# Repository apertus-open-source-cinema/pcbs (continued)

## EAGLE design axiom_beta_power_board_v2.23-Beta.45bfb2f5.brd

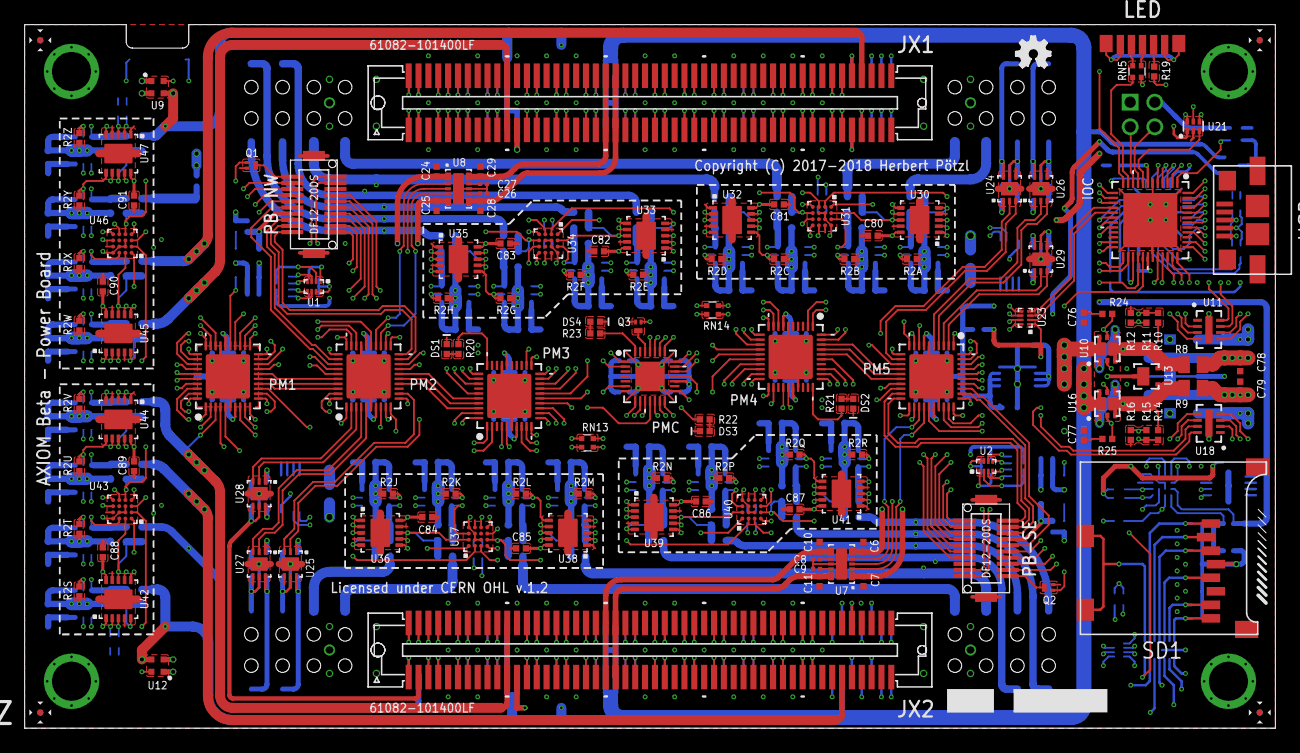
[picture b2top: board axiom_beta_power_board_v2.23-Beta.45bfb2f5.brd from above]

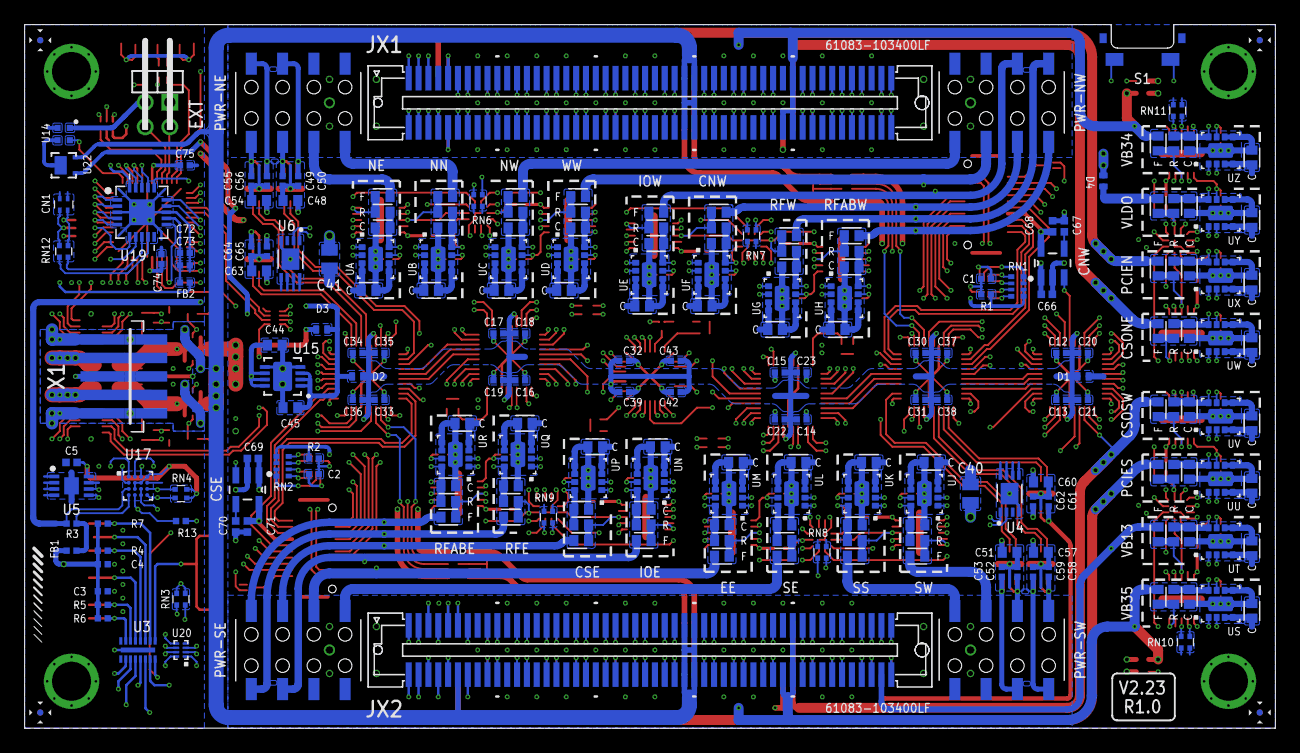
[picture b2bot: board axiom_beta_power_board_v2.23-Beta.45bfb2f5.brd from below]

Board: 4 copper layers, 101.6 x 57.1 mm, 363 parts (231 on the bottom side), 493 nets.

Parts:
BETA: µZ-FCI-SOCKET-NOHOLES-R; µZ-SOCKET-NOHOLES-R
C1, C2, C76, C77, C78, C79: 10n; 0402-C
C1A, C1B, C1C, C1D, C1E, C1F, C1G, C1H, C1J, C1K, C1L, C1M, C1N, C1P, C1Q, C1R, C1S, C1T, C1U, C1V, C1W, C1X, C1Y, C1Z, C2A, C2B, C2C, C2D, C2E, C2F, C2G, C2H, C2J, C2K, C2L, C2M, C2N, C2P, C2Q, C2R, C2S, C2T, C2U, C2V, C2W, C2X, C2Y, C2Z: 0603-C
C3, C49, C50, C52, C53, C55, C56, C58, C59, C61, C62, C64, C65: 1u; 0402-C
C4, C12, C13, C14, C15, C16, C17, C30, C31, C32, C33, C34, C73, C75: 100n; 0402-C
C5: 100n; 0402-B
C6, C7, C10, C11, C24, C25, C28, C29, C80, C81, C82, C83, C84, C85, C86, C87, C88, C89, C90, C91: 0402-C
C8, C9, C26, C27: 0201-C
C18, C19, C20, C21, C22, C23, C35, C36, C37, C38, C39, C72, C74: 4u7; 0402-C
C40, C41: 47u; 0805-C
C42, C43: 10u; 0402-C
C44, C45: 10u; 0603-C
C48, C51, C54, C57, C60, C63: 4u7; 0603-C
C66, C68, C69, C71: 1u; 0402-B
C67, C70: 10n; 0402-B
CN1: CC0504
CNW: SPX3819M5-L; SOT95P280X145-5N
CSE: SPX3819M5-L; SOT95P280X145-5N
D1, D2, D3, D4: PMEG2010BELD; DFN1006D-2
DS1, DS2, DS3, DS4: 0402-C
EXT: 2X02M/90-S
F1, F2, F3, F4, F5, F6, F7, F8: FIDUCIAL; FID_ARROW
FB1, FB2: 0402-C
FBA: 0603-C
FBB: 0603-C
FBC: 0603-C
FBD: 0603-C
FBE: 0603-C
FBF: 0603-C
FBG: 0603-C
FBH: 0603-C
FBJ: 0603-C
FBK: 0603-C
FBL: 0603-C
FBM: 0603-C
FBN: 0603-C
FBP: 0603-C
FBQ: 0603-C
FBR: 0603-C
FBS: 0603-C
FBT: 0603-C
FBU: 0603-C
FBV: 0603-C
FBW: 0603-C
FBX: 0603-C
FBY: 0603-C
FBZ: 0603-C
IOC: PIC16F15386; UQFN50P600X600X100-49N-NSM
LED: MSL0104RGB; MSL0104-SL
LOGO1: OSHW_LOGO_FILLX0100-NT; OSHW_FILLX100_NOTEXT
PB-NW: DF12(XX)-20DP-0.5V
PB-SE: DF12(XX)-20DP-0.5V
PM1, PM2, PM3, PM4, PM5: PIC16F1779-NSM; UQFN40P500X500X100-41N-NSM
PMC: PIC16F15356; UQFN50P400X400X100-29N-NSM
PWR-NE: PINRC-2X04; R2X04
PWR-NW: PINRC-2X04; R2X04
PWR-SE: PINRC-2X04; R2X04
PWR-SW: PINRC-2X04; R2X04
Q1, Q2, Q3: NX3008NBKMB; SOT883(B)
R1, R2: 200k; 0402-C
R1A, R1B, R1C, R1D, R1E, R1F, R1G, R1H, R1J, R1K, R1L, R1M, R1N, R1P, R1Q, R1R, R1S, R1T, R1U, R1V, R1W, R1X, R1Y, R1Z: 0603-C
R2A, R2B, R2C, R2D, R2E, R2F, R2G, R2H, R2J, R2K, R2L, R2M, R2N, R2P, R2Q, R2R, R2S, R2T, R2U, R2V, R2W, R2X, R2Y, R2Z, R3, R13, R19, R20, R21, R22, R23: 0402-C
R4, R5, R6, R7: 50k; 0402-C
R8, R9: 0805-C
R10, R14: 243k; 0402-C
R11, R15, R24, R25: 5k11; 0402-C
R12, R16: 24k9; 0402-C
RN1, RN2: 4X0402ARV341
RN3, RN4, RN5, RN6, RN7, RN8, RN9, RN10, RN11, RN12, RN13, RN14: EXB24V
S1: SKSNLAE010
SD1: MICRO-SD-2CD; TF-MICRO-SD_PP2
U1, U2: PCA9306; UDFN-8
U3: IP4251CZ16-8-TTL; SON40P135X330X55-17N
U4, U6: MCP9808; DFN-8
U5: BR24G04NUX; DFN200X300X100-9N
U7, U8: AP22966; V-DFN3020-14
U9, U12, U14: MIC94040; MLF-4
U10, U16: NTLUD4C26N; UDFN6
U11, U18: LTC4365; DFN8
U13, U22: PMEG2020CPAS; DFN2020D-3
U15: LT1965; DFN3X3_8LEAD
U17, U31, U34, U37, U40, U43, U46: PAC1934-LP; WLCSP-16-LP
U19: FT231-NSM; QFN65P400X400X100-21N-NSM
U20, U23: TXS0102; X2SON-8
U21: FXLH1T45; MICROPAK-6
U24, U25, U26, U27, U28, U29: AP7312-3333FM-7; DFN2018-6
U30, U32, U33, U35, U36, U38, U39, U41, U42, U44, U45, U47: MCP46X2; DFN-10
UA: TPS82085; MICROSIP
UB: TPS82085; MICROSIP
UC: TPS82085; MICROSIP
UD: TPS82085; MICROSIP
UE: TPS82085; MICROSIP
UF: TPS82085; MICROSIP
UG: TPS82085; MICROSIP
UH: TPS82085; MICROSIP
UJ: TPS82085; MICROSIP
UK: TPS82085; MICROSIP
UL: TPS82085; MICROSIP
UM: TPS82085; MICROSIP
UN: TPS82085; MICROSIP
UP: TPS82085; MICROSIP
UQ: TPS82085; MICROSIP
UR: TPS82085; MICROSIP
US: TPS82085; MICROSIP
USB: 5_USB_3S; MICRO-AB-H-SMT
UT: TPS82085; MICROSIP
UU: TPS82085; MICROSIP
UV: TPS82085; MICROSIP
UW: TPS82085; MICROSIP
UX: TPS82085; MICROSIP
UY: TPS82085; MICROSIP
UZ: TPS82085; MICROSIP
X1: PICO-SPOX-5
ZED: µZ-FCI-CONONLY; µZ-CONONLY

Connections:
!ALERT: PM5.22, U17.C3, U17.D3
!MCLR_1: PM1.16, PM2.36
!MCLR_2: PM2.16, PM3.36
!MCLR_3: PM3.16, PMC.2
!MCLR_4: PM4.16, PMC.1
!MCLR_5: PM4.36, PM5.16
!MCLR_C: PMC.26, Q3.3
!RESET: IOC.27, U19.11
ANY_IN: C44.1, U13.3, U13.4, U15.6, U15.7, U15.8
A_!RST: PB-NW.1, Q1.3
A_RST: PM2.25, Q1.1
A_SCL: PB-NW.2, RN1.1, U1.3
A_SDA: PB-NW.4, RN1.2, U1.4
BACK_1: PM1.13, PMC.10
BACK_5: PM5.13, PMC.18
BANK13_00_N: BETA.89, ZED.89
BANK13_00_P: BETA.87, ZED.87
BANK13_01_N: BETA.90, ZED.90
BANK13_01_P: BETA.88, ZED.88
BANK13_02_N: BETA.93, ZED.93
BANK13_02_P: BETA.91, ZED.91
BANK13_03_N: BETA.94, ZED.94
BANK13_03_P: BETA.92, ZED.92
BANK13_04_N: BETA.195, ZED.195
BANK13_04_P: BETA.193, ZED.193
BANK13_05_N: BETA.196, ZED.196
BANK13_05_P: BETA.194, ZED.194
BANK13_06_N: BETA.199, ZED.199
BANK13_06_P: BETA.197, ZED.197
BANK13_SE_0: BETA.200, ZED.200
BETA_5V: C1A.1, C1B.1, C1C.1, C1D.1, C1E.1, C1F.1, C1G.1, C1H.1, C1J.1, C1K.1, C1L.1, C1M.1, C1N.1, C1P.1, C1Q.1, C1R.1, C1S.1, C1T.1, C1U.1, C1V.1, C1W.1, C1X.1, C1Y.1, C1Z.1, C5.1, C6.1, C7.1, C24.1, C25.1, C40.1, C41.1, C80.1, C81.1, C82.1, C83.1, C84.1, C85.1, C86.1, C87.1, C88.1, C89.1, C90.1, C91.1, D1.A, RN4.3, RN4.4, RN6.3, RN6.4, RN7.3, RN7.4, RN8.3, RN8.4, RN9.3, RN9.4, RN10.3, RN10.4, RN11.3, RN11.4, U4.5, U4.6, U4.7, U4.8, U5.8, U6.5, U6.6, U6.7, U6.8, U7.1, U7.3, U7.5, U8.1, U8.3, U8.5, U10.6, U10.D1, U11.6, U17.A4, U17.B2, U17.B3, U17.C2, U30.1, U30.10, U31.A4, U31.B2, U31.B3, U31.C2, U32.9, U32.10, U33.1, U33.10, U34.A4, U34.B2, U34.B3, U34.C2, U35.9, U35.10, U36.1, U36.10, U37.A4, U37.B2, U37.B3, U37.C2, U38.9, U38.10, U39.1, U39.10, U40.A4, U40.B2, U40.B3, U40.C2, U41.9, U41.10, U42.1, U42.10, U43.A4, U43.B2, U43.B3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
BETA_!FAULT: IOC.40, U11.7
BETA_!SHDN: IOC.37, U11.8
BETA_GATE: R24.1, U10.2, U10.5, U11.5
BETA_IN: R8.2, R10.1, U10.3, U10.D2, U11.4, U13.2, U17.B1
BETA_OV: R11.2, R12.1, U11.2
BETA_SUP: C78.1, R8.1, U17.A1, X1.4, X1.4A
BETA_UV: R10.2, R11.1, U11.3
BTN: PM1.20, S1.2
B_!RST: PB-SE.1, Q2.3
B_RST: PM5.25, Q2.1
B_SCL: PB-SE.2, RN2.1, U2.3
B_SDA: PB-SE.4, RN2.2, U2.4
CBUS3: IOC.28, U19.16
CC_!MCLR: IOC.20, U19.7
CC_JX1: IOC.8, U21.3
CC_PCLK: IOC.18, U19.15
CC_PDAT: IOC.19, U19.14
CC_SE_0: IOC.47, U20.6
CC_SE_1: IOC.48, U20.7
CD: SD1.CD1, SD1.CD2, U3.1
CD': IOC.26, U3.16
CLK: SD1.5, U3.5
CMD: R4.2, SD1.3, U3.4
CNW_BYP: C67.1, CNW.4
CNW_EN: CNW.3, PM1.25
CSE_BYP: C70.1, CSE.4
CSE_EN: CSE.3, PM5.36
CSO_NE_V: BETA.7, FBX.2, PM1.37
CSO_NW_V: FBF.2, PM3.32, PWR-NW.6
CSO_SE_V: FBP.2, PM4.32, PWR-SE.6
CSO_SW_V: BETA.112, FBU.2, PM1.2
D0: IOC.5, U19.17
D1: IOC.45, U19.1
D2: IOC.3, U19.19
D3: IOC.2, U19.6
D4: IOC.4, U19.18
D5: IOC.43, U19.4
D6: IOC.42, U19.5
D7: IOC.44, U19.2
DAT0: R5.2, SD1.7, U3.6
DAT1: R6.2, SD1.8, U3.7
DAT2: R7.2, SD1.1, U3.2
DAT3: SD1.2, U3.3
DM: RN12.3, U19.9
DP: RN12.4, U19.8
DS1: PM3.30, R20.1
DS2: PM4.30, R21.1
DS3: PMC.6, R22.1
DS4: PMC.28, R23.1
DXP_0_N: BETA.100, ZED.100
DXP_0_P: BETA.98, ZED.98
EN_3: PM2.24, U8.2
EN_4: PM2.23, U8.4
EN_5: PM5.24, U7.2
EN_6: PM5.23, U7.4
EN_A: PM4.40, UA.1
EN_B: PM4.2, UB.1
EN_C: PM4.10, UC.1
EN_D: PM4.12, UD.1
EN_E: PM3.18, UE.1
EN_F: PM3.20, UF.1
EN_G: PM3.22, UG.1
EN_H: PM3.33, UH.1
EN_J: PM3.40, UJ.1
EN_K: PM3.2, UK.1
EN_L: PM3.10, UL.1
EN_M: PM3.12, UM.1
EN_N: PM4.18, UN.1
EN_P: PM4.20, UP.1
EN_Q: PM4.22, UQ.1
EN_R: PM4.33, UR.1
EN_S: PM1.17, US.1
EN_T: PM1.5, UT.1
EN_U: PM1.4, UU.1
EN_V: PM1.36, UV.1
EN_W: PM1.34, UW.1
EN_X: PM1.30, UX.1
EN_Y: PM1.28, UY.1
EN_Z: PM1.21, UZ.1
EXTA: EXT.2, IOC.10
EXTB: EXT.4, IOC.9
E_B_SCL: PM5.31, RN2.4, U2.6
E_B_SDA: PM5.30, RN2.3, U2.5
E_I2C_EN: PM5.17, U24.2
E_I2C_V: C50.1, PWR-NE.6, U24.6
E_SPI_EN: PM5.5, U26.2
E_SPI_V: C56.1, PWR-NE.8, U26.6
E_VE: FBM.2, PM5.21, PWR-SE.4
E_VE_CV: PB-SE.20, PM5.18
E_VE_OV: PB-SE.9, PM5.10
E_VE_UV: PB-SE.11, PM5.33
FAN_SUP: EXT.3, U14.1
FAN_SUP_EN: IOC.1, U14.4
FB_A: R2A.2, U30.6, UA.7
FB_B: R2B.2, U30.7, UB.7
FB_C: R2C.2, U32.6, UC.7
FB_D: R2D.2, U32.7, UD.7
FB_E: R2E.2, U33.6, UE.7
FB_F: R2F.2, U33.7, UF.7
FB_G: R2G.2, U35.6, UG.7
FB_H: R2H.2, U35.7, UH.7
FB_J: R2J.2, U36.6, UJ.7
FB_K: R2K.2, U36.7, UK.7
FB_L: R2L.2, U38.6, UL.7
FB_M: R2M.2, U38.7, UM.7
FB_N: R2N.2, U39.6, UN.7
FB_P: R2P.2, U39.7, UP.7
FB_Q: R2Q.2, U41.6, UQ.7
FB_R: R2R.2, U41.7, UR.7
FB_S: R2S.2, U42.6, US.7
FB_T: R2T.2, U42.7, UT.7
FB_U: R2U.2, U44.6, UU.7
FB_V: R2V.2, U44.7, UV.7
FB_W: R2W.2, U45.6, UW.7
FB_X: R2X.2, U45.7, UX.7
FB_Y: R2Y.2, U47.6, UY.7
FB_Z: R2Z.2, U47.7, UZ.7
GND: BETA.15, BETA.16, BETA.21, BETA.22, BETA.27, BETA.28, BETA.33, BETA.34, BETA.39, BETA.40, BETA.45, BETA.46, BETA.51, BETA.52, BETA.65, BETA.66, BETA.71, BETA.72, BETA.77, BETA.85, BETA.86, BETA.95, BETA.96, BETA.115, BETA.116, BETA.121, BETA.122, BETA.127, BETA.128, BETA.133, BETA.134, BETA.139, BETA.140, BETA.145, BETA.146, BETA.151, BETA.152, BETA.165, BETA.166, BETA.171, BETA.172, BETA.177, BETA.185, BETA.186, BETA.191, BETA.192, C1.2, C1A.2, C1B.2, C1C.2, C1D.2, C1E.2, C1F.2, C1G.2, C1H.2, C1J.2, C1K.2, C1L.2, C1M.2, C1N.2, C1P.2, C1Q.2, C1R.2, C1S.2, C1T.2, C1U.2, C1V.2, C1W.2, C1X.2, C1Y.2, C1Z.2, C2.2, C2A.2, C2B.2, C2C.2, C2D.2, C2E.2, C2F.2, C2G.2, C2H.2, C2J.2, C2K.2, C2L.2, C2M.2, C2N.2, C2P.2, C2Q.2, C2R.2, C2S.2, C2T.2, C2U.2, C2V.2, C2W.2, C2X.2, C2Y.2, C2Z.2, C3.2, C4.2, C5.2, C6.2, C7.2, C8.2, C9.2, C10.2, C11.2, C12.2, C13.2, C14.2, C15.2, C16.2, C17.2, C18.2, C19.2, C20.2, C21.2, C22.2, C23.2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
IOE_V: FBN.2, PM4.35, PWR-SE.5, RN2.7, RN2.8, U2.2
IOW_V: FBE.2, PM3.35, PWR-NW.5, RN1.7, RN1.8, U1.2
JTAG_EN: PM2.5, U27.2
JTAG_V: C59.1, PWR-SW.8, U27.6
JX1_00_N: BETA.13, ZED.13
JX1_00_P: BETA.11, ZED.11
JX1_01_N: BETA.14, ZED.14
JX1_01_P: BETA.12, ZED.12
JX1_02_N: BETA.19, ZED.19
JX1_02_P: BETA.17, ZED.17
JX1_03_N: BETA.20, ZED.20
JX1_03_P: BETA.18, ZED.18
JX1_04_N: BETA.25, ZED.25
JX1_04_P: BETA.23, ZED.23
JX1_05_N: BETA.26, ZED.26
JX1_05_P: BETA.24, ZED.24
JX1_06_N: BETA.31, ZED.31
JX1_06_P: BETA.29, ZED.29
JX1_07_N: BETA.32, ZED.32
JX1_07_P: BETA.30, ZED.30
JX1_08_N: BETA.37, ZED.37
JX1_08_P: BETA.35, ZED.35
JX1_09_N: BETA.38, ZED.38
JX1_09_P: BETA.36, ZED.36
JX1_10_N: BETA.43, ZED.43
JX1_10_P: BETA.41, ZED.41
JX1_11_N: BETA.44, ZED.44
JX1_11_P: BETA.42, ZED.42
JX1_12_N: BETA.49, ZED.49
JX1_12_P: BETA.47, ZED.47
JX1_13_N: BETA.50, ZED.50
JX1_13_P: BETA.48, ZED.48
JX1_14_N: BETA.55, ZED.55
JX1_14_P: BETA.53, ZED.53
JX1_15_N: BETA.56, ZED.56
JX1_15_P: BETA.54, ZED.54
JX1_16_N: BETA.63, ZED.63
JX1_16_P: BETA.61, ZED.61
JX1_17_N: BETA.64, ZED.64
JX1_17_P: BETA.62, ZED.62
JX1_18_N: BETA.69, ZED.69
JX1_18_P: BETA.67, ZED.67
JX1_19_N: BETA.70, ZED.70
JX1_19_P: BETA.68, ZED.68
JX1_20_N: BETA.75, ZED.75
JX1_20_P: BETA.73, ZED.73
JX1_21_N: BETA.76, ZED.76
JX1_21_P: BETA.74, ZED.74
JX1_22_N: BETA.83, ZED.83
JX1_22_P: BETA.81, ZED.81
JX1_23_N: BETA.84, ZED.84
JX1_23_P: BETA.82, ZED.82
JX1_DIR: IOC.38, U21.5
JX1_SE_0: BETA.9, ZED.9
JX1_SE_1: BETA.10, U21.4, ZED.10
JX2_00_N: BETA.119, ZED.119
JX2_00_P: BETA.117, ZED.117
JX2_01_N: BETA.120, ZED.120
JX2_01_P: BETA.118, ZED.118
JX2_02_N: BETA.125, ZED.125
JX2_02_P: BETA.123, ZED.123
JX2_03_N: BETA.126, ZED.126
JX2_03_P: BETA.124, ZED.124
JX2_04_N: BETA.131, ZED.131
JX2_04_P: BETA.129, ZED.129
JX2_05_N: BETA.132, ZED.132
JX2_05_P: BETA.130, ZED.130
JX2_06_N: BETA.137, ZED.137
JX2_06_P: BETA.135, ZED.135
JX2_07_N: BETA.138, ZED.138
JX2_07_P: BETA.136, ZED.136
JX2_08_N: BETA.143, ZED.143
JX2_08_P: BETA.141, ZED.141
JX2_09_N: BETA.144, ZED.144
JX2_09_P: BETA.142, ZED.142
JX2_10_N: BETA.149, ZED.149
JX2_10_P: BETA.147, ZED.147
JX2_11_N: BETA.150, ZED.150
JX2_11_P: BETA.148, ZED.148
JX2_12_N: BETA.155, ZED.155
JX2_12_P: BETA.153, ZED.153
JX2_13_N: BETA.156, ZED.156
JX2_13_P: BETA.154, ZED.154
JX2_14_N: BETA.163, ZED.163
JX2_14_P: BETA.161, ZED.161
JX2_15_N: BETA.164, ZED.164
JX2_15_P: BETA.162, ZED.162
JX2_16_N: BETA.169, ZED.169
JX2_16_P: BETA.167, ZED.167
JX2_17_N: BETA.170, ZED.170
JX2_17_P: BETA.168, ZED.168
JX2_18_N: BETA.175, ZED.175
JX2_18_P: BETA.173, ZED.173
JX2_19_N: BETA.176, ZED.176
JX2_19_P: BETA.174, ZED.174
JX2_20_N: BETA.183, ZED.183
JX2_20_P: BETA.181, ZED.181
JX2_21_N: BETA.184, ZED.184
JX2_21_P: BETA.182, ZED.182
JX2_22_N: BETA.189, ZED.189
JX2_22_P: BETA.187, ZED.187
JX2_23_N: BETA.190, ZED.190
JX2_23_P: BETA.188, ZED.188
JX2_SE_0: U20.3, ZED.113
JX2_SE_1: U20.2, ZED.114
LED_B: IOC.11, RN5.3
LED_G: IOC.33, R19.2
LED_G': LED.3, R19.1
LED_R: IOC.32, RN5.4
MEAS_A: FBA.1, R1A.2, U30.5, U31.B1
MEAS_B: FBB.1, R1B.2, U30.8, U31.A2
MEAS_C: FBC.1, R1C.2, U31.D2, U32.5
MEAS_D: FBD.1, R1D.2, U31.C1, U32.8
MEAS_E: FBE.1, R1E.2, U33.5, U34.B1
MEAS_F: FBF.1, R1F.2, U33.8, U34.A2
MEAS_G: FBG.1, R1G.2, U34.D2, U35.5
MEAS_H: FBH.1, R1H.2, U34.C1, U35.8
MEAS_J: FBJ.1, R1J.2, U36.5, U37.B1
MEAS_K: FBK.1, R1K.2, U36.8, U37.A2
MEAS_L: FBL.1, R1L.2, U37.D2, U38.5
MEAS_M: FBM.1, R1M.2, U37.C1, U38.8
MEAS_N: FBN.1, R1N.2, U39.5, U40.B1
MEAS_P: FBP.1, R1P.2, U39.8, U40.A2
MEAS_Q: FBQ.1, R1Q.2, U40.D2, U41.5
MEAS_R: FBR.1, R1R.2, U40.C1, U41.8
MEAS_S: FBS.1, R1S.2, U42.5, U43.B1
MEAS_T: FBT.1, R1T.2, U42.8, U43.A2
MEAS_U: FBU.1, R1U.2, U43.D2, U44.5
MEAS_V: FBV.1, R1V.2, U43.C1, U44.8
MEAS_W: FBW.1, R1W.2, U45.5, U46.B1
MEAS_X: FBX.1, R1X.2, U45.8, U46.A2
MEAS_Y: FBY.1, R1Y.2, U46.D2, U47.5
MEAS_Z: FBZ.1, R1Z.2, U46.C1, U47.8
MIX_SUP: U14.3, U22.3, U22.4
unnamed: DS2.1, R21.2
unnamed: DS4.1, R23.2
unnamed: C3.1, C4.1, FB1.2, R4.1, R5.1, R6.1, R7.1, SD1.4
unnamed: LED.4, RN5.1
unnamed: C76.1, R24.2
unnamed: LED.5, RN5.2
unnamed: CN1.3, RN12.2, USB.2
unnamed: C77.1, R25.2
unnamed: CN1.4, RN12.1, USB.3
unnamed: U10.1, U10.4
unnamed: C26.1, U8.7
unnamed: C27.1, U8.9
unnamed: C8.1, U7.7
unnamed: C9.1, U7.9
unnamed: DS1.1, R20.2
unnamed: DS3.1, R22.2
unnamed: C1.1, R1.2, U1.7, U1.8
unnamed: C2.1, R2.2, U2.7, U2.8
unnamed: U16.1, U16.4
N_CHK_V: C68.1, CNW.5, PB-NW.13
N_I2C_EN: PM5.4, U26.3
N_I2C_V: C55.1, PWR-NE.7, U26.5
N_SPI_EN: PM5.12, U24.3
N_SPI_V: C49.1, PWR-NE.5, U24.5
N_VE: FBA.2, PWR-NE.3
N_VE_CV: PB-NW.18, PM2.9
N_VE_OV: PB-NW.7, PM2.8
N_VE_RS: PB-NW.8, PM2.11
N_VE_UV: PB-NW.19, PM2.19
N_VN: FBB.2, PWR-NE.1
N_VN_CV: PB-NW.16, PM2.35
N_VN_OV: PB-NW.5, PM2.29
N_VN_RS: PB-NW.12, PM2.34
N_VN_UV: PB-NW.17, PM2.20
N_VW: FBC.2, PWR-NW.2
N_VW_CV: PB-NW.14, PM2.40
N_VW_OV: PB-NW.3, PM2.28
N_VW_RS: PB-NW.10, PM2.39
N_VW_UV: PB-NW.15, PM2.32
PCIE_I2C_EN: PM2.2, U28.3
PCIE_I2C_V: BETA.198, C61.1, U28.5
PCIE_NIO_EN: PM1.23, U9.4
PCIE_N_5V: BETA.59, BETA.60, C29.1, U8.10
PCIE_N_V: BETA.79, BETA.80, FBW.2, PM1.11
PCIE_N_VCCIO: BETA.78, U9.1
PCIE_SIO_EN: PM1.24, U12.4
PCIE_S_5V: BETA.159, BETA.160, C10.1, U7.6
PCIE_S_V: BETA.179, BETA.180, FBV.2, PM1.3
PCIE_S_VCCIO: BETA.178, U12.1
PCLK_1: PM1.14, PM2.38
PCLK_2: PM2.14, PM3.38
PCLK_3: PM3.14, PMC.11
PCLK_4: PM4.14, PMC.14
PCLK_5: PM4.38, PM5.14
PCLK_C: PMC.24, U23.7
PDAT_1: PM1.15, PM2.37
PDAT_2: PM2.15, PM3.37
PDAT_3: PM3.15, PMC.15
PDAT_4: PM4.15, PMC.19
PDAT_5: PM4.37, PM5.15
PDAT_C: PMC.25, U23.6
PEX_N_V: BETA.57, BETA.58, C28.1, U8.6
PEX_S_V: BETA.157, BETA.158, C11.1, U7.10
PG_1V8: RN13.2, ZED.110
PG_1V8': PM3.4, RN13.3
PG_A: PM4.39, UA.2
PG_B: PM4.1, UB.2
PG_C: PM4.8, UC.2
PG_D: PM4.11, UD.2
PG_E: PM3.17, UE.2
PG_F: PM3.19, UF.2
PG_G: PM3.21, UG.2
PG_H: PM3.31, UH.2
PG_J: PM3.39, UJ.2
PG_K: PM3.1, UK.2
PG_L: PM3.8, UL.2
PG_M: PM3.11, UM.2
PG_MODULE: RN13.1, ZED.111
PG_MODULE': PM3.5, RN13.4
PG_N: PM4.17, UN.2
PG_P: PM4.19, UP.2
PG_Q: PM4.21, UQ.2
PG_R: PM4.31, UR.2
PG_S: PM1.12, US.2
PG_T: PM1.8, UT.2
PG_U: PM1.9, UU.2
PG_V: PM1.10, UV.2
PG_W: PM1.33, UW.2
PG_X: PM1.29, UX.2
PG_Y: PM1.19, UY.2
PG_Z: PM1.22, UZ.2
PMOD_D0: U3.10, ZED.101
PMOD_D1: U3.11, ZED.102
PMOD_D2: U3.13, ZED.103
PMOD_D3: U3.12, ZED.104
PMOD_D6: U3.15, ZED.107
PMOD_D7: U3.14, ZED.108
PMOD_SCL: IOC.34, RN3.1, ZED.105
PMOD_SDA: IOC.35, RN3.2, ZED.106
PM_MCLR: IOC.29, Q3.1
PM_PCLK: IOC.17, U23.2
PM_PDAT: IOC.16, U23.3
RFAB_E_V: FBR.2, PM4.13, PWR-SE.8
RFAB_W_V: FBH.2, PM3.13, PWR-NW.8
RFE_V: FBQ.2, PM4.9, PWR-SE.7
RFW_V: FBG.2, PM3.9, PWR-NW.7
SCL1: PMC.20, RN6.2, U6.2, U30.2, U31.C4, U32.2
SCL2: PMC.23, RN7.2, U33.2, U34.C4, U35.2
SCL3: PMC.9, RN8.2, U4.2, U36.2, U37.C4, U38.2
SCL4: PMC.13, RN9.2, U39.2, U40.C4, U41.2
SCL5: PM1.1, RN10.1, U42.2, U43.C4, U44.2
SCL6: PM1.32, RN11.1, U45.2, U46.C4, U47.2
SCL7: PM5.1, RN4.1, U5.6, U17.C4
SDA1: PMC.21, RN6.1, U6.1, U30.3, U31.D4, U32.3
SDA2: PMC.22, RN7.1, U33.3, U34.D4, U35.3
SDA3: PMC.8, RN8.1, U4.1, U36.3, U37.D4, U38.3
SDA4: PMC.12, RN9.1, U39.3, U40.D4, U41.3
SDA5: PM1.39, RN10.2, U42.3, U43.D4, U44.3
SDA6: PM1.31, RN11.2, U45.3, U46.D4, U47.3
SDA7: PM5.38, RN4.2, U5.5, U17.D4
SD_MEAS: FB1.1, R3.2, U17.D1
SD_V: C64.1, R3.1, U17.C1, U29.5
SD_V_EN: PM5.2, U29.3
SENSE: R13.2, U17.D2, X1.3, X1.3A
SIGNAL: PM5.37, R13.1
S_CHK_V: C71.1, CSE.5, PB-SE.13
S_I2C_EN: PM2.4, U27.3
S_I2C_V: C58.1, PWR-SW.7, U27.5
S_SPI_EN: PM2.12, U25.3
S_SPI_V: C52.1, PWR-SW.5, U25.5
S_VE: FBL.2, PWR-SE.2
S_VE_CV: PB-SE.14, PM5.40
S_VE_OV: PB-SE.3, PM5.28
S_VE_RS: PB-SE.10, PM5.39
S_VE_UV: PB-SE.15, PM5.32
S_VS: FBK.2, PWR-SW.1
S_VS_CV: PB-SE.16, PM5.35
S_VS_OV: PB-SE.5, PM5.29
S_VS_RS: PB-SE.12, PM5.34
S_VS_UV: PB-SE.17, PM5.20
S_VW: FBJ.2, PWR-SW.3
S_VW_CV: PB-SE.18, PM5.9
S_VW_OV: PB-SE.7, PM5.8
S_VW_RS: PB-SE.8, PM5.11
S_VW_UV: PB-SE.19, PM5.19
UNUSED_EN: PM2.3, U28.2
UNUSED_V: C62.1, U28.6
V33: C45.1, D2.A, D3.A, U15.1, U15.2, U15.3, U22.1
VBUS: FB2.2, USB.1
VCC: C65.1, C74.1, C75.1, D3.C, IOC.7, IOC.30, LED.1, LED.2, LED.6, LED.7, RN3.3, RN3.4, U19.20, U20.8, U21.1, U23.1, U23.5, U29.6
VCCO_13: FBT.2, PM1.38, ZED.198
VCCO_34: FBZ.2, PM1.35, U9.3, U21.6, ZED.78, ZED.79, ZED.80
VCCO_35: FBS.2, PM1.40, U12.3, U20.1, U20.5, ZED.178, ZED.179, ZED.180
VCC_EN: PM5.3, U29.2
VLDO: C48.1, C51.1, C54.1, C57.1, C60.1, C63.1, C66.1, C69.1, CNW.1, CSE.1, D4.C, PM1.18, U24.1, U25.1, U26.1, U27.1, U28.1, U29.1
VLDO': D4.A, FBY.2
VOUT_A: C2A.1, R1A.1, U31.A1, UA.8
VOUT_B: C2B.1, R1B.1, U31.A3, UB.8
VOUT_C: C2C.1, R1C.1, U31.D3, UC.8
VOUT_D: C2D.1, R1D.1, U31.D1, UD.8
VOUT_E: C2E.1, R1E.1, U34.A1, UE.8
VOUT_F: C2F.1, R1F.1, U34.A3, UF.8
VOUT_G: C2G.1, R1G.1, U34.D3, UG.8
VOUT_H: C2H.1, R1H.1, U34.D1, UH.8
VOUT_J: C2J.1, R1J.1, U37.A1, UJ.8
VOUT_K: C2K.1, R1K.1, U37.A3, UK.8
VOUT_L: C2L.1, R1L.1, U37.D3, UL.8
VOUT_M: C2M.1, R1M.1, U37.D1, UM.8
VOUT_N: C2N.1, R1N.1, U40.A1, UN.8
VOUT_P: C2P.1, R1P.1, U40.A3, UP.8
VOUT_Q: C2Q.1, R1Q.1, U40.D3, UQ.8
VOUT_R: C2R.1, R1R.1, U40.D1, UR.8
VOUT_S: C2S.1, R1S.1, U43.A1, US.8
VOUT_T: C2T.1, R1T.1, U43.A3, UT.8
VOUT_U: C2U.1, R1U.1, U43.D3, UU.8
VOUT_V: C2V.1, R1V.1, U43.D1, UV.8
VOUT_W: C2W.1, R1W.1, U46.A1, UW.8
VOUT_X: C2X.1, R1X.1, U46.A3, UX.8
VOUT_Y: C2Y.1, R1Y.1, U46.D3, UY.8
VOUT_Z: C2Z.1, R1Z.1, U46.D1, UZ.8
VPC: C12.1, C13.1, C14.1, C15.1, C16.1, C17.1, C18.1, C19.1, C20.1, C21.1, C22.1, C23.1, C30.1, C31.1, C32.1, C33.1, C34.1, C35.1, C36.1, C37.1, C38.1, C39.1, C42.1, C43.1, D1.C, D2.C, PM1.7, PM1.26, PM2.7, PM2.26, PM3.7, PM3.26, PM4.7, PM4.26, PM5.7, PM5.26, PMC.17, R1.1, R2.1, RN1.5, RN1.6, RN2.5, RN2.6, U23.8
VP_0_N: BETA.99, RN14.2, ZED.99
VP_0_N': PM4.25, RN14.3
VP_0_P: BETA.97, RN14.1, ZED.97
VP_0_P': PM4.24, RN14.4
VUSB: C72.1, C73.1, FB2.1, U19.12
W_A_SCL: PM2.31, RN1.4, U1.6
W_A_SDA: PM2.30, RN1.3, U1.5
W_I2C_EN: PM2.17, U25.2
W_I2C_V: C53.1, PWR-SW.6, U25.6
W_VW: FBD.2, PM2.21, PWR-NW.4
W_VW_CV: PB-NW.20, PM2.18
W_VW_OV: PB-NW.9, PM2.10
W_VW_UV: PB-NW.11, PM2.33
ZED_5V: U16.6, U16.D1, U18.6, U22.2, ZED.57, ZED.58, ZED.59, ZED.60, ZED.112, ZED.157, ZED.158, ZED.159, ZED.160
ZED_!FAULT: IOC.41, U18.7
ZED_!INIT: BETA.109, ZED.109
ZED_!SHDN: IOC.36, U18.8
ZED_!SRST: IOC.24, ZED.6
ZED_DONE: BETA.8, IOC.25, ZED.8
ZED_GATE: R25.1, U16.2, U16.5, U18.5
ZED_IN: R9.2, R14.1, U13.1, U16.3, U16.D2, U17.A2, U18.4
ZED_OV: R15.2, R16.1, U18.2
ZED_PWR_EN: IOC.23, ZED.5
ZED_SUP: C79.1, R9.1, U17.A3, X1.2, X1.2A
ZED_TCK: IOC.13, ZED.1
ZED_TDI: IOC.15, ZED.4
ZED_TDO: IOC.12, ZED.3
ZED_TMS: IOC.14, ZED.2
ZED_UV: R14.2, R15.1, U18.3

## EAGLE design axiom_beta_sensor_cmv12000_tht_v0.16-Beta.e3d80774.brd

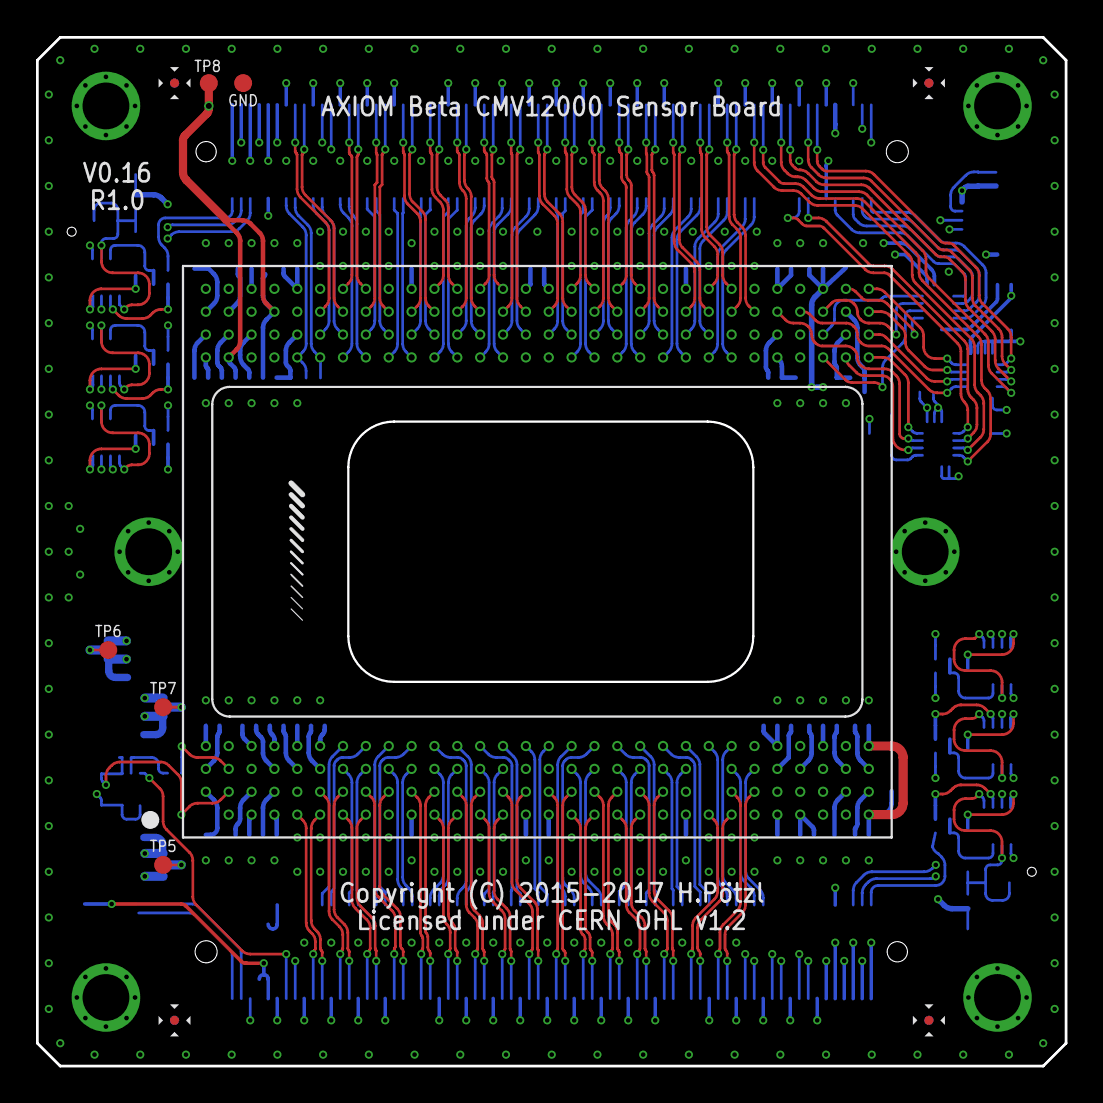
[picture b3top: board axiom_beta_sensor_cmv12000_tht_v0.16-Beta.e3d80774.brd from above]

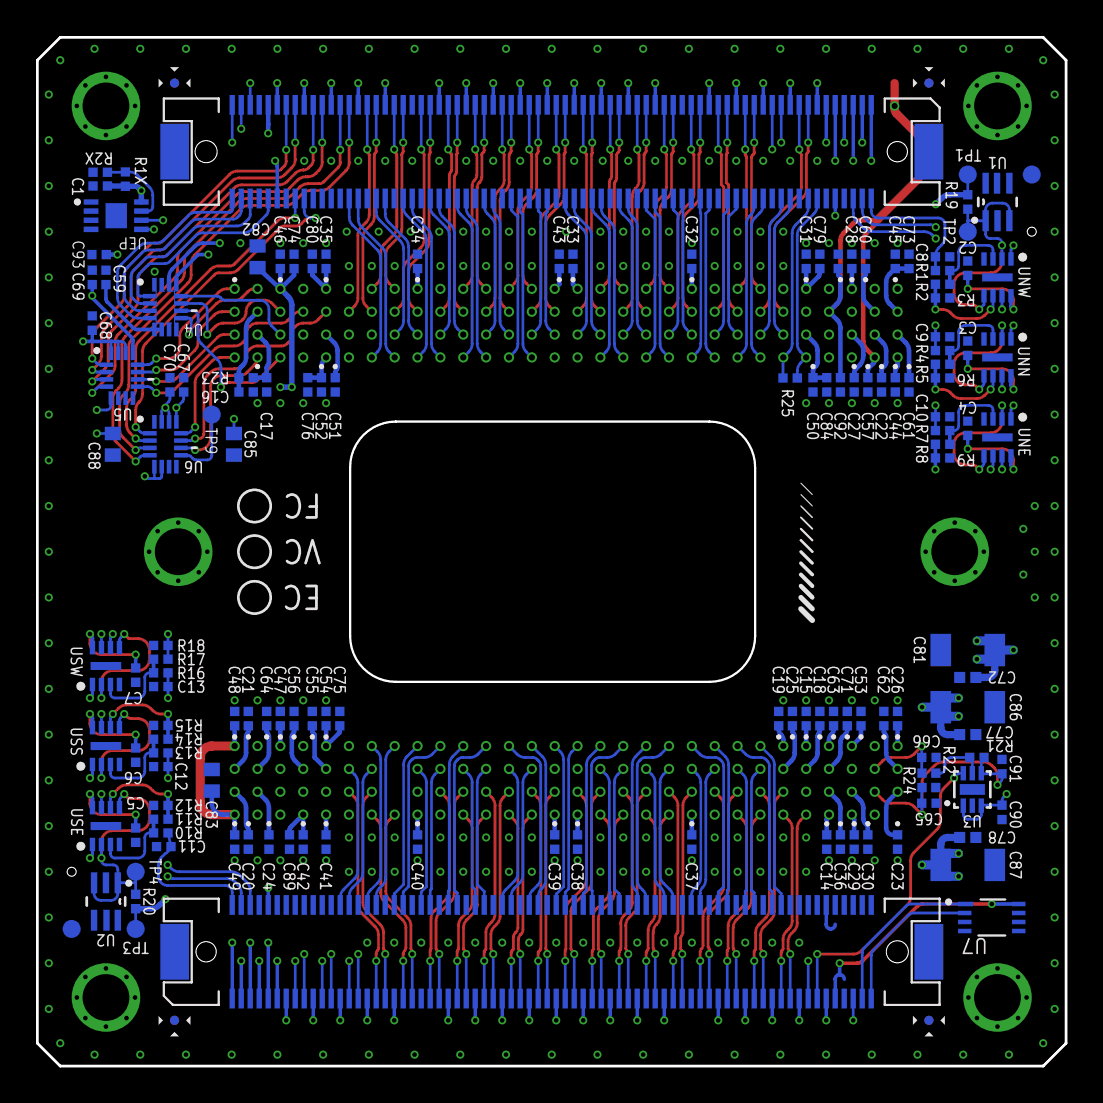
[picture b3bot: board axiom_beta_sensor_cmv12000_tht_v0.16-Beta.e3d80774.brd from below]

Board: 4 copper layers, 57.1 x 57.1 mm, 151 parts (143 on the bottom side), 234 nets.

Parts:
C1, C2, C3, C4, C5, C6, C7, C14, C15, C16, C17, C18, C19, C20, C21, C22, C23, C24, C25, C26, C27, C28, C29, C30, C31, C32, C33, C34, C35, C36, C37, C38, C39, C40, C41, C42, C43, C44, C45, C46, C47, C48, C49, C50, C51, C52, C53, C54, C55, C56, C57, C58, C59, C60, C61, C62, C63, C64, C65, C66, C67, C68, C69, C70, C71, C93: 100n; 0402-C
C8, C9, C10, C11, C12, C13: 1µ; 0402-C
C72, C77, C78: 4µ7; 0402-B
C73, C74, C75, C76, C79, C80, C84, C89, C90, C91, C92: 4µ7; 0402-C
C81, C86, C87: 100µ; 1206-B
C82, C83, C85, C88: 10µ; 0603-C
GND, GND75, GND77: TPTP10R; TP10R
PARALLELLA: PARALLELLA-FRAME
R1, R7: 28k7; 0402-C
R1X, R2X, R10, R11, R12: 0402-C
R2, R8: 3k32; 0402-C
R3, R9, R15, R18: 16k9; 0402-C
R4: 15k4; 0402-C
R5: 3k09; 0402-C
R6: 30k9; 0402-C
R13: 22k6; 0402-C
R14: 9k53; 0402-C
R16: 18k7; 0402-C
R17: 13k3; 0402-C
R19, R20: 18k; 0402-C
R21: 5k9; 0402-C
R22: 14k3; 0402-C
R23, R24: 0R; 0402-C
R25: 100R; 0402-C
SENSOR: CMV12000ANDON-CREAM; 10-30-07-237-400T4-CREAM
TP1, TP2, TP3, TP4, TP5, TP6, TP7, TP8, TP9: TPTP10R; TP10R
U1, U2: TLV431DCK; SOT65P210X110-6N
U3: MIC47050; MLF-6
U4, U5, U6: SN74AVC4T774RSV; QFN40P185X265X55-16N
U7: LM75BGD; SOT996-2/3
U$1: µZ-FRAME
UEP: BR24G04NUX; DFN200X300X100-9N
UNE: TS332IQ2T; DFN200X200X100-9N
UNN: TS332IQ2T; DFN200X200X100-9N
UNW: TS332IQ2T; DFN200X200X100-9N
USE: TS332IQ2T; DFN200X200X100-9N
USS: TS332IQ2T; DFN200X200X100-9N
USW: TS332IQ2T; DFN200X200X100-9N
X-NORTH: FX10-144P; FX10A-144P
X-SOUTH: FX10-144P; FX10A-144P

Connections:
CLK_IN: SENSOR.E30, U6.12
FRAME_REQ: SENSOR.G30, U5.11
GND: C1.2, C2.2, C3.2, C4.2, C5.2, C6.2, C7.2, C8.2, C9.2, C10.2, C11.2, C12.2, C13.2, C14.2, C15.2, C16.2, C17.2, C18.2, C19.2, C20.2, C21.2, C22.1, C23.1, C24.1, C25.1, C26.1, C27.1, C28.1, C29.2, C30.2, C31.2, C32.2, C33.2, C34.2, C35.2, C36.2, C37.2, C38.2, C39.2, C40.2, C41.2, C42.2, C43.2, C44.2, C45.2, C46.2, C47.2, C48.2, C49.2, C50.2, C51.2, C52.2, C53.2, C54.2, C55.2, C56.2, C57.2, C58.2, C59.2, C60.2, C61.2, C62.2, C63.2, C64.2, C65.2, C66.2, C67.2, C68.2, C69.2, C70.2, C71.2, C72.2, C73.2, C74.2, C75.2, C76.2, C77.2, C78.2, C79.2, C80.2, C81.2, C82.2, C83.2, C84.2, C85.2, C86.2, C87.2, C88.2, C89.2, C90.2, C91.1, C92.2, C93.2, GND.TP, GND75.TP, GND77.TP, R2X.2, R3.2, R6.2, R9.2, R12.2, R15.2, R18.2, R22.1, SENSOR.A9, SENSOR.A21, SENSOR.A25, SENSOR.A28, SENSOR.A29, SENSOR.B5, SENSOR.B22, SENSOR.B26, SENSOR.B27, SENSOR.B28, SENSOR.C15, SENSOR.C16, SENSOR.C28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
N00_N: R25.2, SENSOR.E6, X-NORTH.16
N00_P: R25.1, SENSOR.E5, X-NORTH.14
N01_N: SENSOR.G7, X-NORTH.17
N01_P: SENSOR.G6, X-NORTH.15
N02_N: SENSOR.F7, X-NORTH.22
N02_P: SENSOR.F6, X-NORTH.20
N04_N: SENSOR.E8, X-NORTH.28
N04_P: SENSOR.E7, X-NORTH.26
N05_N: SENSOR.H8, X-NORTH.29
N05_P: SENSOR.H7, X-NORTH.27
N06_N: SENSOR.F9, X-NORTH.34
N06_P: SENSOR.F8, X-NORTH.32
N07_N: SENSOR.G9, X-NORTH.35
N07_P: SENSOR.G8, X-NORTH.33
N08_N: SENSOR.E10, X-NORTH.40
N08_P: SENSOR.E9, X-NORTH.38
N09_N: SENSOR.G11, X-NORTH.41
N09_P: SENSOR.G10, X-NORTH.39
N10_N: SENSOR.F11, X-NORTH.46
N10_P: SENSOR.F10, X-NORTH.44
N11_N: SENSOR.H12, X-NORTH.47
N11_P: SENSOR.H11, X-NORTH.45
N12_N: SENSOR.E12, X-NORTH.52
N12_P: SENSOR.E11, X-NORTH.50
N13_N: SENSOR.G13, X-NORTH.53
N13_P: SENSOR.G12, X-NORTH.51
N14_N: SENSOR.F13, X-NORTH.58
N14_P: SENSOR.F12, X-NORTH.56
N15_N: SENSOR.H14, X-NORTH.59
N15_P: SENSOR.H13, X-NORTH.57
N16_N: SENSOR.E14, X-NORTH.64
N16_P: SENSOR.E13, X-NORTH.62
N17_N: SENSOR.G15, X-NORTH.65
N17_P: SENSOR.G14, X-NORTH.63
N18_N: SENSOR.F15, X-NORTH.70
N18_P: SENSOR.F14, X-NORTH.68
N19_N: SENSOR.G17, X-NORTH.71
N19_P: SENSOR.G16, X-NORTH.69
N20_N: SENSOR.F17, X-NORTH.76
N20_P: SENSOR.F16, X-NORTH.74
N21_N: SENSOR.H18, X-NORTH.77
N21_P: SENSOR.H17, X-NORTH.75
N22_N: SENSOR.E18, X-NORTH.82
N22_P: SENSOR.E17, X-NORTH.80
N23_N: SENSOR.G19, X-NORTH.83
N23_P: SENSOR.G18, X-NORTH.81
N24_N: SENSOR.F19, X-NORTH.88
N24_P: SENSOR.F18, X-NORTH.86
N25_N: SENSOR.H20, X-NORTH.89
N25_P: SENSOR.H19, X-NORTH.87
N26_N: SENSOR.E20, X-NORTH.94
N26_P: SENSOR.E19, X-NORTH.92
N27_N: SENSOR.G21, X-NORTH.95
N27_P: SENSOR.G20, X-NORTH.93
N28_N: SENSOR.F21, X-NORTH.100
N28_P: SENSOR.F20, X-NORTH.98
N29_N: SENSOR.G23, X-NORTH.101
N29_P: SENSOR.G22, X-NORTH.99
N30_N: SENSOR.E22, X-NORTH.106
N30_P: SENSOR.E21, X-NORTH.104
N31_N: SENSOR.H24, X-NORTH.107
N31_P: SENSOR.H23, X-NORTH.105
N32_N: SENSOR.F23, X-NORTH.112
N32_P: SENSOR.F22, X-NORTH.110
N33_N: SENSOR.G25, X-NORTH.113
N33_P: SENSOR.G24, X-NORTH.111
N34_N: SENSOR.E24, X-NORTH.118
N34_P: SENSOR.E23, X-NORTH.116
N35_N: U6.4, X-NORTH.119
N35_P: U6.3, X-NORTH.117
N37_N: U5.3, X-NORTH.125
N37_P: U5.4, X-NORTH.123
N38_N: U6.2, X-NORTH.130
N38_P: U6.1, X-NORTH.128
N39_N: U5.1, X-NORTH.131
N39_P: U5.2, X-NORTH.129
unnamed: R1X.2, R2X.1, UEP.7
unnamed: C60.1, SENSOR.G2
unnamed: C61.1, SENSOR.F1
unnamed: TP9.TP, U6.9
unnamed: C62.1, SENSOR.C1
unnamed: C63.1, SENSOR.D4
unnamed: C64.1, SENSOR.C29
unnamed: C71.1, SENSOR.C4
unnamed: C14.1, SENSOR.A4
unnamed: C15.1, SENSOR.D5
unnamed: R21.1, R22.2, U3.5
unnamed: C18.1, SENSOR.C5
unnamed: C19.1, SENSOR.D6
unnamed: C20.1, SENSOR.B30
unnamed: C21.1, SENSOR.C30
unnamed: C22.2, SENSOR.F2
unnamed: C23.2, SENSOR.B1
unnamed: C24.2, SENSOR.B29
unnamed: C25.2, SENSOR.C6
unnamed: C26.2, SENSOR.D1
unnamed: C27.2, SENSOR.F3
unnamed: C28.2, SENSOR.H3
unnamed: C29.1, SENSOR.A3
unnamed: C30.1, SENSOR.B3
unnamed: R11.2, R12.1, USE.6
unnamed: R5.2, R6.1, UNN.6
unnamed: R8.2, R9.1, UNE.6
unnamed: R10.2, R11.1, USE.3
unnamed: R7.2, R8.1, UNE.3
unnamed: R1.2, R2.1, UNW.3
unnamed: R2.2, R3.1, UNW.6
unnamed: R14.2, R15.1, USS.6
unnamed: R13.2, R14.1, USS.3
unnamed: R16.2, R17.1, USW.3
unnamed: R17.2, R18.1, USW.6
N_CHK_V: C2.1, C3.1, C4.1, R19.1, TP1.TP, UNE.8, UNN.8, UNW.8, X-NORTH.10
N_I2C_V: C1.1, R1X.1, UEP.8, X-NORTH.135
N_REF: R19.2, TP2.TP, U1.1, U1.3, UNE.2, UNE.5, UNN.2, UNN.5, UNW.2, UNW.5
N_SCK: U4.4, X-NORTH.144
N_SCL: UEP.6, X-NORTH.143
N_SDA: UEP.5, X-NORTH.141
N_SDI: U4.2, X-NORTH.140
N_SDO: U4.3, X-NORTH.142
N_SPI_EN: U4.1, X-NORTH.136
N_SPI_V: C59.1, U4.5, U4.6, U4.14, U4.15, X-NORTH.134
N_VE: C50.1, C51.1, C52.1, C53.1, C54.1, C55.1, C56.1, C67.1, C69.1, C75.1, C76.1, C77.1, C84.1, C85.1, C86.1, C93.1, SENSOR.C26, SENSOR.C27, SENSOR.D3, SENSOR.D26, SENSOR.E26, SENSOR.F5, SENSOR.F26, TP7.TP, U4.13, U5.13, U6.13, X-NORTH.109, X-NORTH.115, X-NORTH.121, X-NORTH.127, X-NORTH.133
N_VE_CV: C10.1, R7.1, X-NORTH.6
N_VE_OV: UNE.7, X-NORTH.5
N_VE_UV: UNE.1, X-NORTH.11
N_VN: C31.1, C32.1, C33.1, C34.1, C35.1, C36.1, C37.1, C38.1, C39.1, C40.1, C41.1, C42.1, C43.1, C44.1, C68.1, C70.1, C78.1, C79.1, C80.1, C87.1, C88.1, C89.1, SENSOR.A10, SENSOR.A15, SENSOR.A16, SENSOR.A22, SENSOR.A26, SENSOR.A27, SENSOR.B4, SENSOR.E1, SENSOR.H5, SENSOR.H10, SENSOR.H15, SENSOR.H16, SENSOR.H22, SENSOR.H26, TP5.TP, U5.5, U5.14, U5.15, U5.16, U6.5, U6.6, U6.14, U6.15, X-NORTH.49, X-NORTH.55, X-NORTH.61, X-NORTH.67, X-NORTH.73, X-NORTH.79, X-NORTH.85, X-NORTH.91, X-NORTH.97
N_VN_CV: C9.1, R4.1, X-NORTH.4
N_VN_OV: UNN.7, X-NORTH.3
N_VN_UV: UNN.1, X-NORTH.9
N_VW: C57.1, C58.1, C92.1, SENSOR.E2, SENSOR.G4, TP8.TP, X-NORTH.13, X-NORTH.19, X-NORTH.25, X-NORTH.31, X-NORTH.37
N_VW_CV: C8.1, R1.1, X-NORTH.2
N_VW_OV: UNW.7, X-NORTH.1
N_VW_UV: UNW.1, X-NORTH.7
R5: R4.2, R5.1, UNN.3
S04_N: SENSOR.C24, X-SOUTH.28
S04_P: SENSOR.C25, X-SOUTH.26
S06_N: SENSOR.D23, X-SOUTH.34
S06_P: SENSOR.D24, X-SOUTH.32
S07_N: SENSOR.B24, X-SOUTH.35
S07_P: SENSOR.B25, X-SOUTH.33
S08_N: SENSOR.D21, X-SOUTH.40
S08_P: SENSOR.D22, X-SOUTH.38
S09_N: SENSOR.A23, X-SOUTH.41
S09_P: SENSOR.A24, X-SOUTH.39
S10_N: SENSOR.C21, X-SOUTH.46
S10_P: SENSOR.C22, X-SOUTH.44
S11_N: SENSOR.B20, X-SOUTH.47
S11_P: SENSOR.B21, X-SOUTH.45
S12_N: SENSOR.D19, X-SOUTH.52
S12_P: SENSOR.D20, X-SOUTH.50
S13_N: SENSOR.A19, X-SOUTH.53
S13_P: SENSOR.A20, X-SOUTH.51
S14_N: SENSOR.C19, X-SOUTH.58
S14_P: SENSOR.C20, X-SOUTH.56
S15_N: SENSOR.B18, X-SOUTH.59
S15_P: SENSOR.B19, X-SOUTH.57
S16_N: SENSOR.C17, X-SOUTH.64
S16_P: SENSOR.C18, X-SOUTH.62
S17_N: SENSOR.A17, X-SOUTH.65
S17_P: SENSOR.A18, X-SOUTH.63
S18_N: SENSOR.D17, X-SOUTH.70
S18_P: SENSOR.D18, X-SOUTH.68
S19_N: SENSOR.B16, X-SOUTH.71
S19_P: SENSOR.B17, X-SOUTH.69
S20_N: SENSOR.D15, X-SOUTH.76
S20_P: SENSOR.D16, X-SOUTH.74
S21_N: SENSOR.B14, X-SOUTH.77
S21_P: SENSOR.B15, X-SOUTH.75
S22_N: SENSOR.D13, X-SOUTH.82
S22_P: SENSOR.D14, X-SOUTH.80
S23_N: SENSOR.A13, X-SOUTH.83
S23_P: SENSOR.A14, X-SOUTH.81
S24_N: SENSOR.C13, X-SOUTH.88
S24_P: SENSOR.C14, X-SOUTH.86
S25_N: SENSOR.B12, X-SOUTH.89
S25_P: SENSOR.B13, X-SOUTH.87
S26_N: SENSOR.D11, X-SOUTH.94
S26_P: SENSOR.D12, X-SOUTH.92
S27_N: SENSOR.A11, X-SOUTH.95
S27_P: SENSOR.A12, X-SOUTH.93
S28_N: SENSOR.C11, X-SOUTH.100
S28_P: SENSOR.C12, X-SOUTH.98
S29_N: SENSOR.B10, X-SOUTH.101
S29_P: SENSOR.B11, X-SOUTH.99
S30_N: SENSOR.C9, X-SOUTH.106
S30_P: SENSOR.C10, X-SOUTH.104
S31_N: SENSOR.B8, X-SOUTH.107
S31_P: SENSOR.B9, X-SOUTH.105
S32_N: SENSOR.D9, X-SOUTH.112
S32_P: SENSOR.D10, X-SOUTH.110
S33_N: SENSOR.A7, X-SOUTH.113
S33_P: SENSOR.A8, X-SOUTH.111
S34_N: SENSOR.C7, X-SOUTH.118
S34_P: SENSOR.C8, X-SOUTH.116
S35_N: SENSOR.B6, X-SOUTH.119
S35_P: SENSOR.B7, X-SOUTH.117
S36_N: SENSOR.D7, X-SOUTH.124
S36_P: SENSOR.D8, X-SOUTH.122
S37_N: SENSOR.A5, X-SOUTH.125
S37_P: SENSOR.A6, X-SOUTH.123
S39_N: U3.6, X-SOUTH.131
SPI_CLK: SENSOR.H29, U4.9
SPI_EN: SENSOR.F28, U4.12
SPI_IN: SENSOR.E28, U4.10
SPI_OUT: SENSOR.G28, U4.11
SYS_RES_N: SENSOR.F30, U5.10
S_CHK_V: C5.1, C6.1, C7.1, R20.1, TP3.TP, USE.8, USS.8, USW.8, X-SOUTH.10
S_I2C_V: U7.8, X-SOUTH.135
S_REF: R20.2, TP4.TP, U2.1, U2.3, USE.2, USE.5, USS.2, USS.5, USW.2, USW.5
S_SCL: U7.2, X-SOUTH.143
S_SDA: U7.1, X-SOUTH.141
S_VE: X-SOUTH.13, X-SOUTH.19, X-SOUTH.25, X-SOUTH.31, X-SOUTH.37
S_VE_CV: C11.1, R10.1, X-SOUTH.2
S_VE_OV: USE.7, X-SOUTH.1
S_VE_UV: USE.1, X-SOUTH.7
S_VS: C45.1, C46.1, C47.1, C48.1, C49.1, C72.1, C73.1, C74.1, C81.1, C82.1, C83.1, SENSOR.A30, SENSOR.D28, SENSOR.D30, SENSOR.G1, SENSOR.H28, TP6.TP, X-SOUTH.49, X-SOUTH.55, X-SOUTH.61, X-SOUTH.67, X-SOUTH.73, X-SOUTH.79, X-SOUTH.85, X-SOUTH.91, X-SOUTH.97
S_VS_CV: C12.1, R13.1, X-SOUTH.4
S_VS_OV: USS.7, X-SOUTH.3
S_VS_UV: USS.1, X-SOUTH.9
S_VW: C90.1, U3.1, U3.3, X-SOUTH.109, X-SOUTH.115, X-SOUTH.121, X-SOUTH.127, X-SOUTH.133
S_VW_CV: C13.1, R16.1, X-SOUTH.6
S_VW_OV: USW.7, X-SOUTH.5
S_VW_UV: USW.1, X-SOUTH.11
TDIG1: SENSOR.G27, U5.9
TDIG2: SENSOR.G26, U6.11
T_EXP1: SENSOR.H30, U5.12
T_EXP2: SENSOR.E29, U6.10
VRAMP1: C16.1, R23.1, SENSOR.G29
VRAMP2: C17.1, R23.2, SENSOR.F29
VTREF: C65.1, C91.2, R21.2, R24.1, SENSOR.B2, U3.4
VTSIG: C66.1, R24.2, SENSOR.C2
